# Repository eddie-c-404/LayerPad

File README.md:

# LayerPad
Highly customizable macropad for creators.

## Why?
This project was meant to assist me in being more efficient in my day-to-day activities through the use of the shortcut keys and macros which I frequently use. Through the use of programmable keys, several layers, the rotary encoder and an OLED screen, the macropad is able to be programmed for various uses including Visual Studio, Fusion 360, KiCad and Blender. The aim is to have a small but highly customizable productivity aid which can assist anyone in organizing their workspace.
## Features
- 16 programmable mechanical keys

- Rotary encoder with push button

- OLED display

- USB-C connectivity

- Powered by the ATmega32U4

- Compatible with QMK firmware

## 🚧 Build Status 
| Component | Status | 
|------------|--------| 
| PCB Design | 🚧 In Progress | 
| Schematic | 🚧 In Progress | 
| Case Design | 🚧 In Progress | 
| Firmware | ⏳ Planned | 
| Prototype | ⏳ Planned |

## Future Improvements

- RGB underglow

- Multiple rotary encoders

- Wireless (Bluetooth) version

- Aluminum enclosure

- VIA/Vial support

- Low-profile switch version

- Additional OLED animations

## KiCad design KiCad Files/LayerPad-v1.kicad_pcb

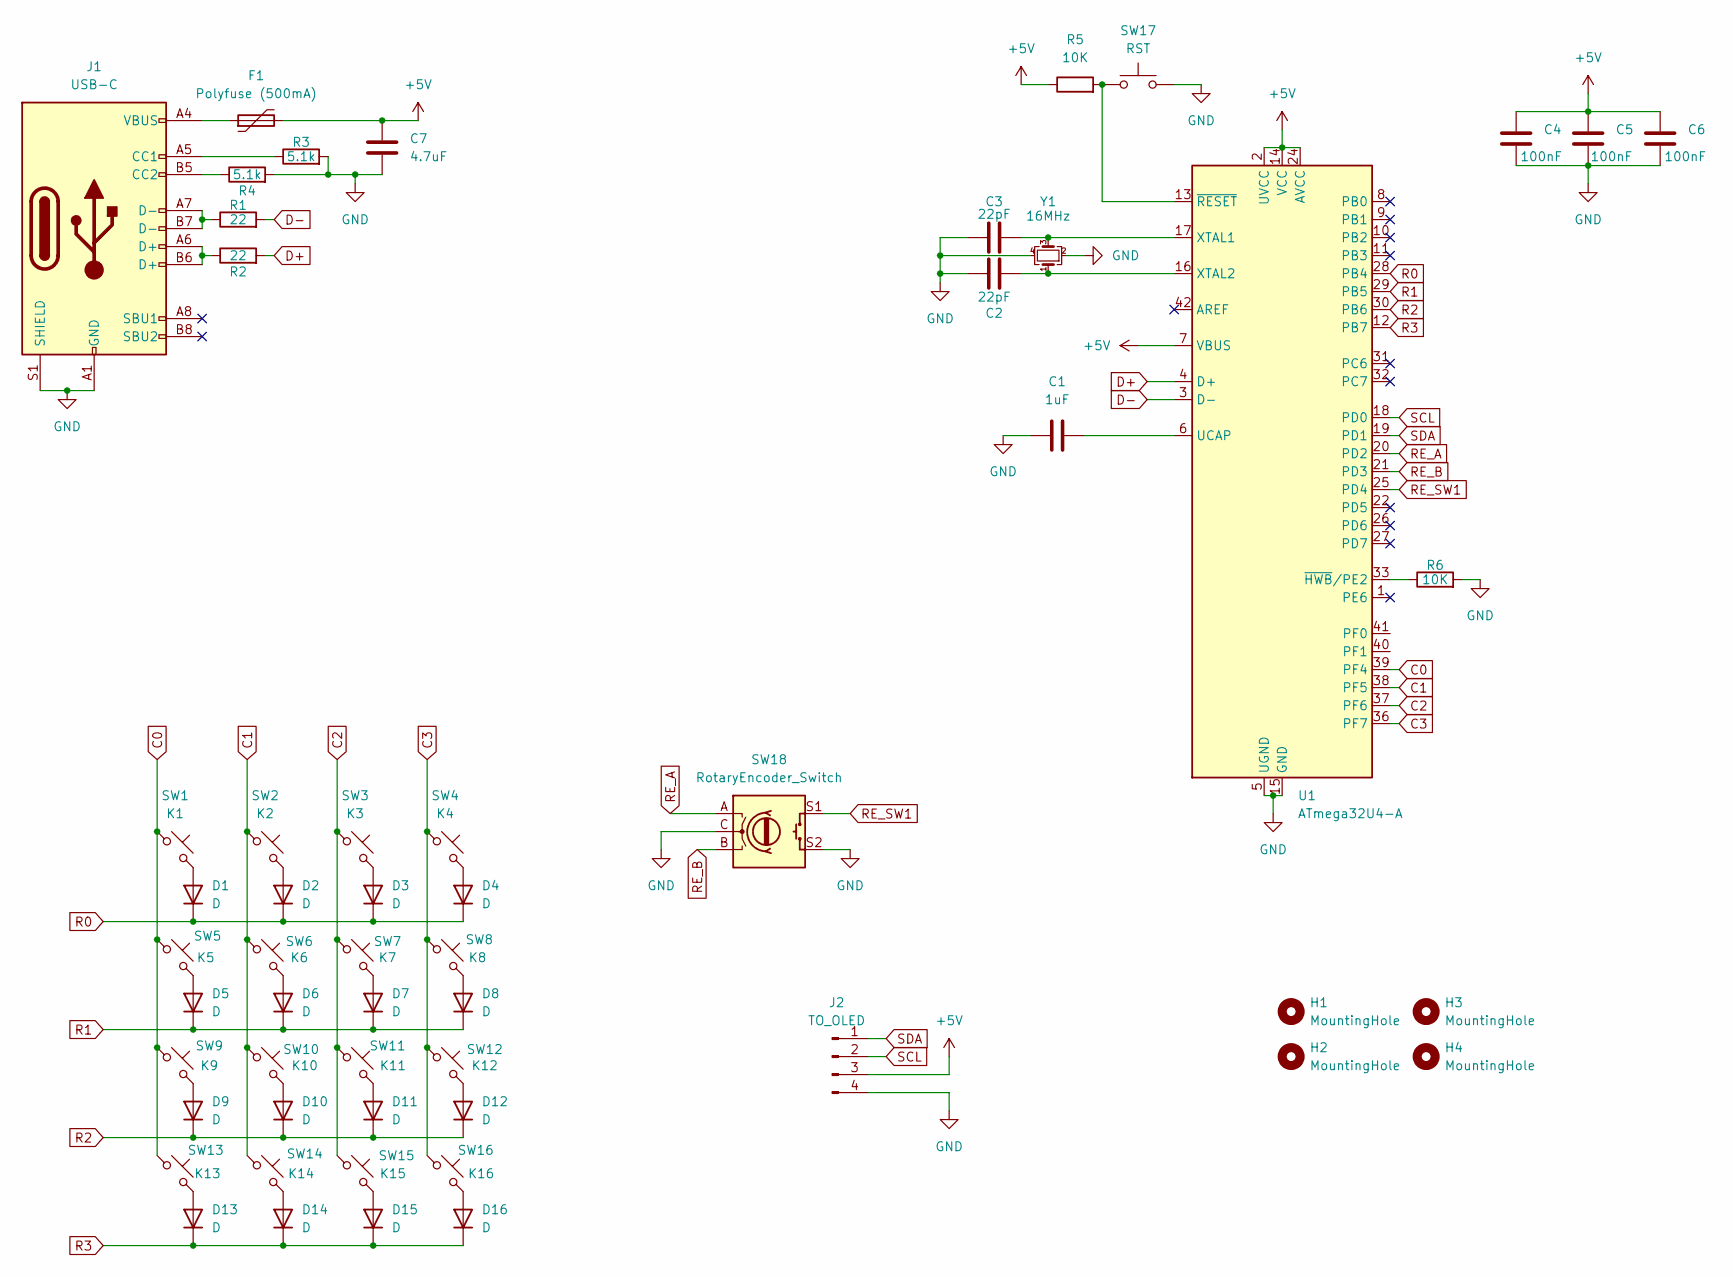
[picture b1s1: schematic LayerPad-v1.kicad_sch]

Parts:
C1: 1uF; C_0603_1608Metric
C2, C3: 22pF; C_0603_1608Metric
C4, C5, C6: 100nF; C_0603_1608Metric
C7: 4.7uF; C_0805_2012Metric
D1, D2, D3, D4, D5, D6, D7, D8, D9, D10, D11, D12, D13, D14, D15, D16: D; D_DO-35_SOD27_P7.62mm_Horizontal
F1: Polyfuse (500mA); Fuse_1206_3216Metric
H1, H2, H3, H4: MountingHole; MountingHole_3.2mm_M3
J1: USB-C; USB_C_Receptacle_G-Switch_GT-USB-7010ASV
J2: TO_OLED; PinHeader_1x04_P2.54mm_Vertical
R1, R2: 22; R_0603_1608Metric
R3, R4: 5.1k; R_0603_1608Metric
R5, R6: 10K; R_0603_1608Metric
SW1: K1; SW_Cherry_MX_1.00u_PCB
SW2: K2; SW_Cherry_MX_1.00u_PCB
SW3: K3; SW_Cherry_MX_1.00u_PCB
SW4: K4; SW_Cherry_MX_1.00u_PCB
SW5: K5; SW_Cherry_MX_1.00u_PCB
SW6: K6; SW_Cherry_MX_1.00u_PCB
SW7: K7; SW_Cherry_MX_1.00u_PCB
SW8: K8; SW_Cherry_MX_1.00u_PCB
SW9: K9; SW_Cherry_MX_1.00u_PCB
SW10: K10; SW_Cherry_MX_1.00u_PCB
SW11: K11; SW_Cherry_MX_1.00u_PCB
SW12: K12; SW_Cherry_MX_1.00u_PCB
SW13: K13; SW_Cherry_MX_1.00u_PCB
SW14: K14; SW_Cherry_MX_1.00u_PCB
SW15: K15; SW_Cherry_MX_1.00u_PCB
SW16: K16; SW_Cherry_MX_1.00u_PCB
SW17: RST; SW_Push_SPST_NO_Alps_SKRK
SW18: RotaryEncoder_Switch; RotaryEncoder_EC11
U1: ATmega32U4-A; TQFP-44_10x10mm_P0.8mm
Y1: 16MHz; Crystal_SMD_0603-4Pin_6.0x3.5mm

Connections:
+5V: C4.1, C5.1, C6.1, C7.1, F1.2, J2.3, R5.1, U1.2 (UVCC), U1.7 (VBUS), U1.14 (VCC), U1.24 (AVCC), U1.34 (VCC), U1.44 (AVCC)
C0: SW1.1, SW5.1, SW9.1, SW13.1, U1.39 (PF4)
C1: SW2.1, SW6.1, SW10.1, SW14.1, U1.38 (PF5)
C2: SW3.1, SW7.1, SW11.1, SW15.1, U1.37 (PF6)
C3: SW4.1, SW8.1, SW12.1, SW16.1, U1.36 (PF7)
D+: R2.2, U1.4 (D+)
D-: R1.2, U1.3 (D-)
GND: C1.1, C2.1, C3.1, C4.2, C5.2, C6.2, C7.2, J1.A1 (GND), J1.A12 (GND), J1.B1 (GND), J1.B12 (GND), J1.S1 (SHIELD), J2.4, R3.2, R4.2, R6.2, SW17.2, SW18.C, SW18.S2, U1.5 (UGND), U1.15 (GND), U1.23 (GND), U1.35 (GND), U1.43 (GND), Y1.2, Y1.4
unnamed: D1.2 (A), SW1.2
unnamed: D2.2 (A), SW2.2
unnamed: D3.2 (A), SW3.2
unnamed: D4.2 (A), SW4.2
unnamed: D5.2 (A), SW5.2
unnamed: D6.2 (A), SW6.2
unnamed: D7.2 (A), SW7.2
unnamed: D8.2 (A), SW8.2
unnamed: D9.2 (A), SW9.2
unnamed: D10.2 (A), SW10.2
unnamed: D11.2 (A), SW11.2
unnamed: D12.2 (A), SW12.2
unnamed: D13.2 (A), SW13.2
unnamed: D14.2 (A), SW14.2
unnamed: D15.2 (A), SW15.2
unnamed: D16.2 (A), SW16.2
unnamed: F1.1, J1.A4 (VBUS), J1.A9 (VBUS), J1.B4 (VBUS), J1.B9 (VBUS)
unnamed: J1.A5 (CC1), R3.1
unnamed: J1.B5 (CC2), R4.1
unnamed: J1.A6 (D+), J1.B6 (D+), R2.1
unnamed: J1.A7 (D-), J1.B7 (D-), R1.1
unnamed: C1.2, U1.6 (UCAP)
unnamed: C3.2, U1.17 (XTAL1), Y1.3
unnamed: C2.2, U1.16 (XTAL2), Y1.1
unnamed: R6.1, U1.33 (~HWB/PE2)
unnamed: R5.2, SW17.1, U1.13 (~RESET)
R0: D1.1 (K), D2.1 (K), D3.1 (K), D4.1 (K), U1.28 (PB4)
R1: D5.1 (K), D6.1 (K), D7.1 (K), D8.1 (K), U1.29 (PB5)
R2: D9.1 (K), D10.1 (K), D11.1 (K), D12.1 (K), U1.30 (PB6)
R3: D13.1 (K), D14.1 (K), D15.1 (K), D16.1 (K), U1.12 (PB7)
RE_A: SW18.A, U1.20 (PD2)
RE_B: SW18.B, U1.21 (PD3)
RE_SW1: SW18.S1, U1.25 (PD4)
SCL: J2.2, U1.18 (PD0)
SDA: J2.1, U1.19 (PD1)

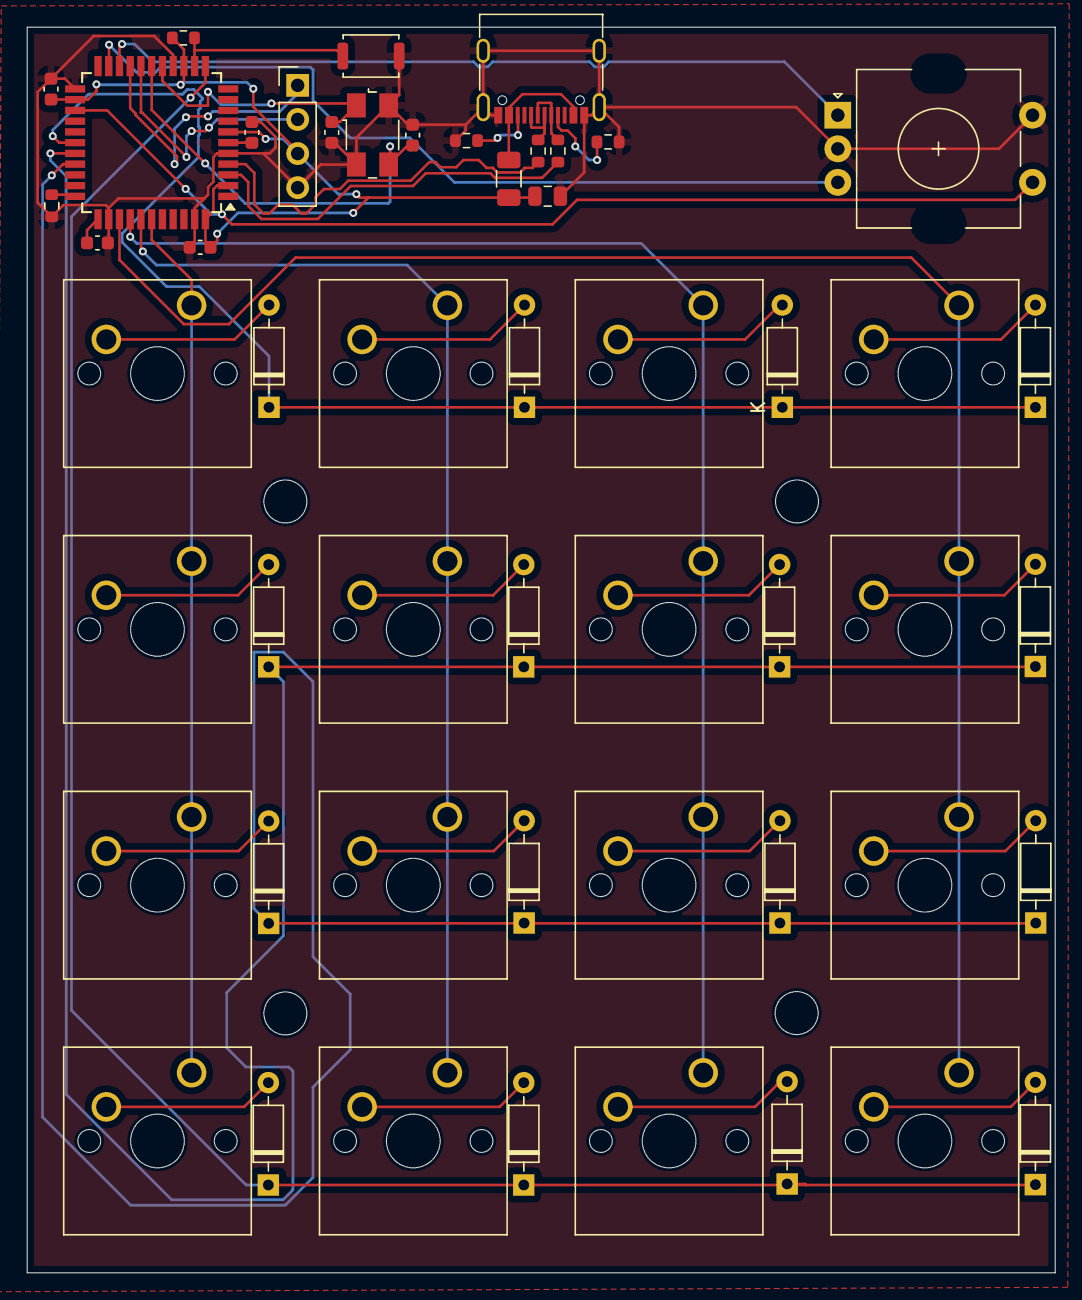
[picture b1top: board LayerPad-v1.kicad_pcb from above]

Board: 2 copper layers, 76.6 x 92.8 mm, 56 parts (0 on the bottom side), 43 nets.
